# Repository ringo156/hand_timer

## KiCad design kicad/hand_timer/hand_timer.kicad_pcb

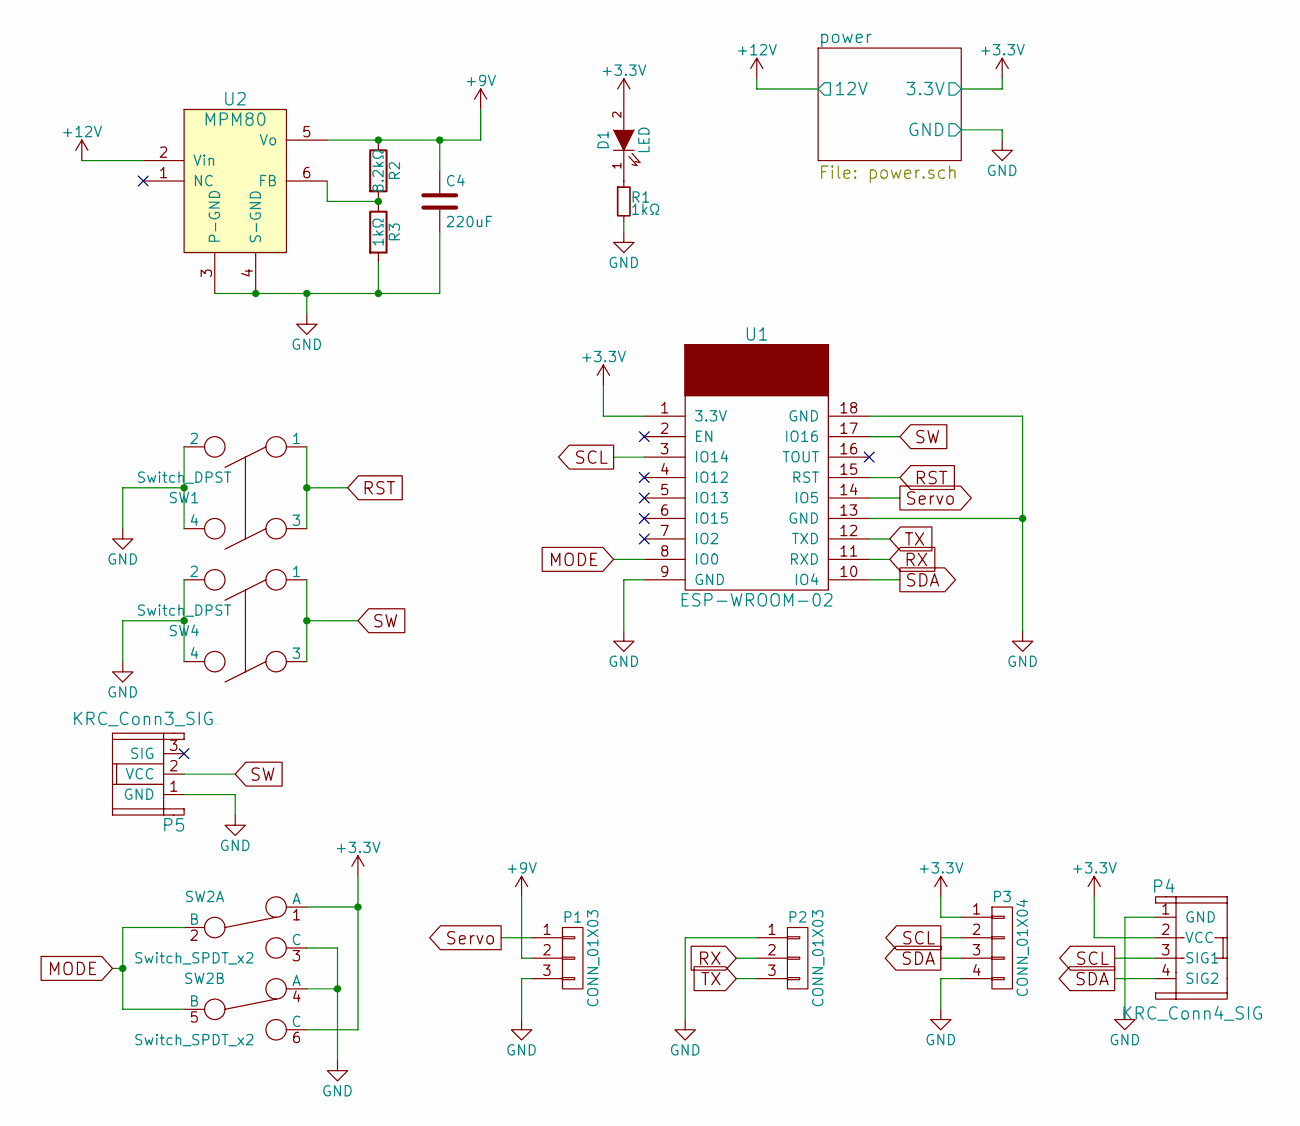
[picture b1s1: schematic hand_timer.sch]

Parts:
C4: 220uF; C_Radial_D10_L13_P5
D1: LED; LED-3MM
P1, P2: CONN_01X03; Socket_Strip_Straight_1x03
P3: CONN_01X04; Socket_Strip_Straight_1x04
P4: KRC_Conn4_SIG; DF1E-4P_Streight
P5: KRC_Conn3_SIG; DF1E-3P_Straight
R1: 1kΩ; R_0603_HandSoldering
R2: 8.2kΩ; Resistor_Horizontal_RM7mm
R3: 1kΩ; Resistor_Horizontal_RM7mm
SW1, SW4: Switch_DPST; tact_switch
SW2: Switch_SPDT_x2; SlideSwitch_DIP
U1: ESP-WROOM-02; ESP-WROOM-02_aitendo
U2: MPM80

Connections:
+3V3: D1.2 (A), P3.1, P4.2 (VCC), SW2.1 (A), SW2.6 (C), U1.1 (3.3V); also elsewhere on the board
+9V: C4.1, P1.2, R2.1, U2.5 (Vo)
+12V: U2.2 (Vin); also elsewhere on the board
GND: C4.2, P1.3, P2.1, P3.4, P4.1 (GND), P5.1 (GND), R1.2, R3.2, SW1.2, SW1.4, SW2.3 (C), SW2.4 (A), SW4.2, SW4.4, U1.9 (GND), U1.13 (GND), U1.18 (GND), U2.3 (P-GND), U2.4 (S-GND); also elsewhere on the board
MODE: SW2.2 (B), SW2.5 (B), U1.8 (IO0)
unnamed: D1.1 (K), R1.1
unnamed: R2.2, R3.1, U2.6 (FB)
RST: SW1.1, SW1.3, U1.15 (RST)
RX: P2.2, U1.11 (RXD)
SCL: P3.2, P4.3 (SIG1), U1.3 (IO14)
SDA: P3.3, P4.4 (SIG2), U1.10 (IO4)
SW: P5.2 (VCC), SW4.1, SW4.3, U1.17 (IO16)
Servo: P1.1, U1.14 (IO5)
TX: P2.3, U1.12 (TXD)

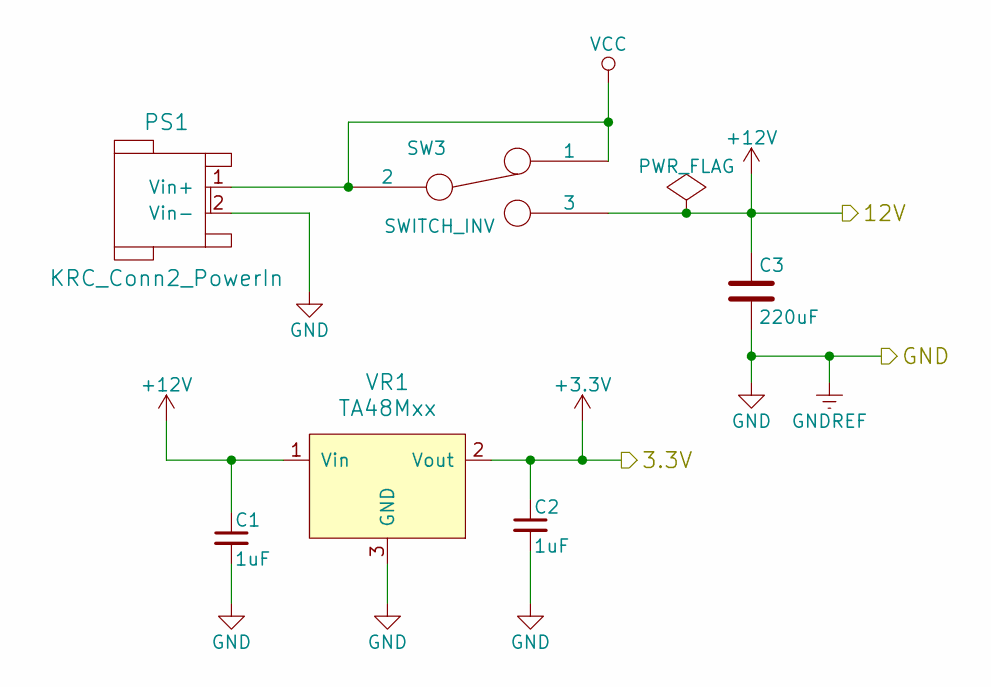
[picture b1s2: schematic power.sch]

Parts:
C1, C2: 1uF; C_0805_HandSoldering
C3: 220uF; C_Radial_D10_L13_P5
PS1: KRC_Conn2_PowerIn; DF22-2P
SW3: SWITCH_INV; Toggle_Switch_1L
VR1: TA48Mxx; TA48m33smd

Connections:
+3V3: C2.1, VR1.2 (Vout); also elsewhere on the board
+12V: C1.1, C3.1, SW3.3, VR1.1 (Vin); also elsewhere on the board
GND: C1.2, C2.2, C3.2, PS1.2 (Vin-), VR1.3 (GND); also elsewhere on the board
VCC: PS1.1 (Vin+), SW3.1, SW3.2

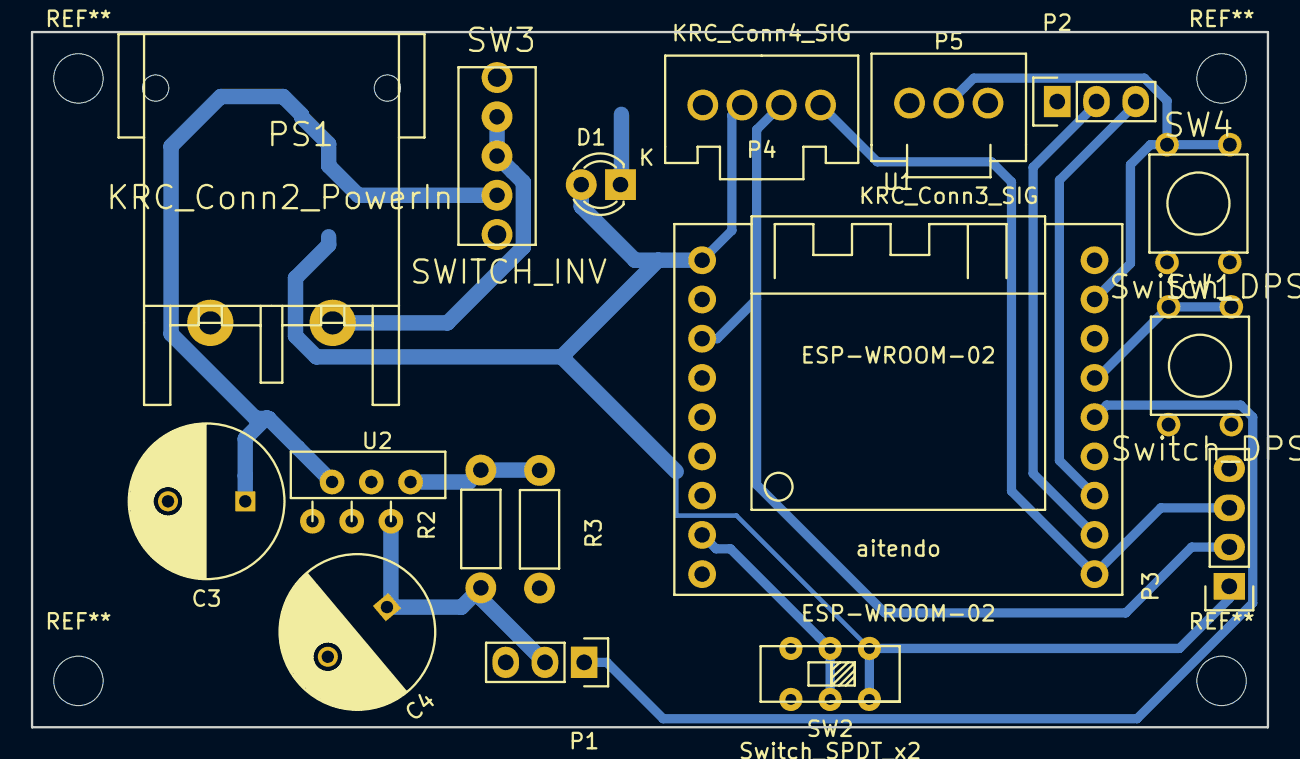
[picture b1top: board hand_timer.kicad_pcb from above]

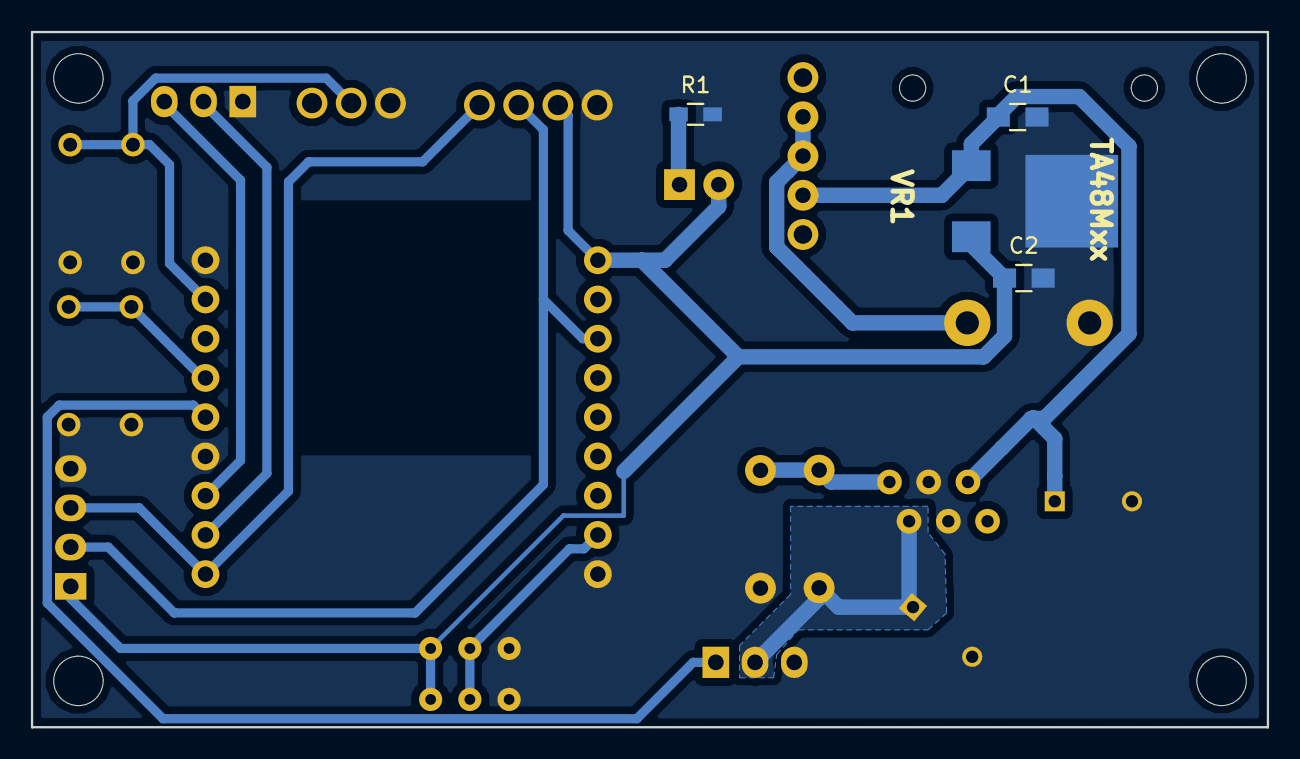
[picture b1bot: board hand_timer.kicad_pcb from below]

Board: 2 copper layers, 80.0 x 45.0 mm, 21 parts (4 on the bottom side), 15 nets.

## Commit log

2016-08-25 upload
2017-06-20 プログラムの整理
2017-06-21 時間指定で動くように改良
2017-06-22 条件式の変更
2017-06-24 スイッチの追加
